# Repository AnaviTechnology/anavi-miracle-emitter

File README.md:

# ANAVI Miracle Emitter

Open source hardware IoT for controlling addressable RGB LED strips (like WS2812B) with XIAO ESP32C3, I2C sensors and mini OLED display.

# License

The project is released under the [Creative Commons Attribution-ShareAlike 4.0 International (CC BY-SA 4.0)](https://creativecommons.org/licenses/by-sa/4.0/).

Note: This is a human-readable summary of (and not a substitute for) the [license](https://creativecommons.org/licenses/by-sa/4.0/legalcode).

You are free to:

Share — copy and redistribute the material in any medium or format Adapt — remix, transform, and build upon the material for any purpose, even commercially. The licensor cannot revoke these freedoms as long as you follow the license terms. Under the following terms:

Attribution — You must give appropriate credit, provide a link to the license, and indicate if changes were made. You may do so in any reasonable manner, but not in any way that suggests the licensor endorses you or your use. ShareAlike — If you remix, transform, or build upon the material, you must distribute your contributions under the same license as the original. No additional restrictions — You may not apply legal terms or technological measures that legally restrict others from doing anything the license permits. Notices:

You do not have to comply with the license for elements of the material in the public domain or where your use is permitted by an applicable exception or limitation. No warranties are given. The license may not give you all of the permissions necessary for your intended use. For example, other rights such as publicity, privacy, or moral rights may limit how you use the material.

You will have to provide a link to the original creator of the project http://www.anavi.technology on any documentation or website.

Credit can be attributed through a link to the creator website: http://www.anavi.technology

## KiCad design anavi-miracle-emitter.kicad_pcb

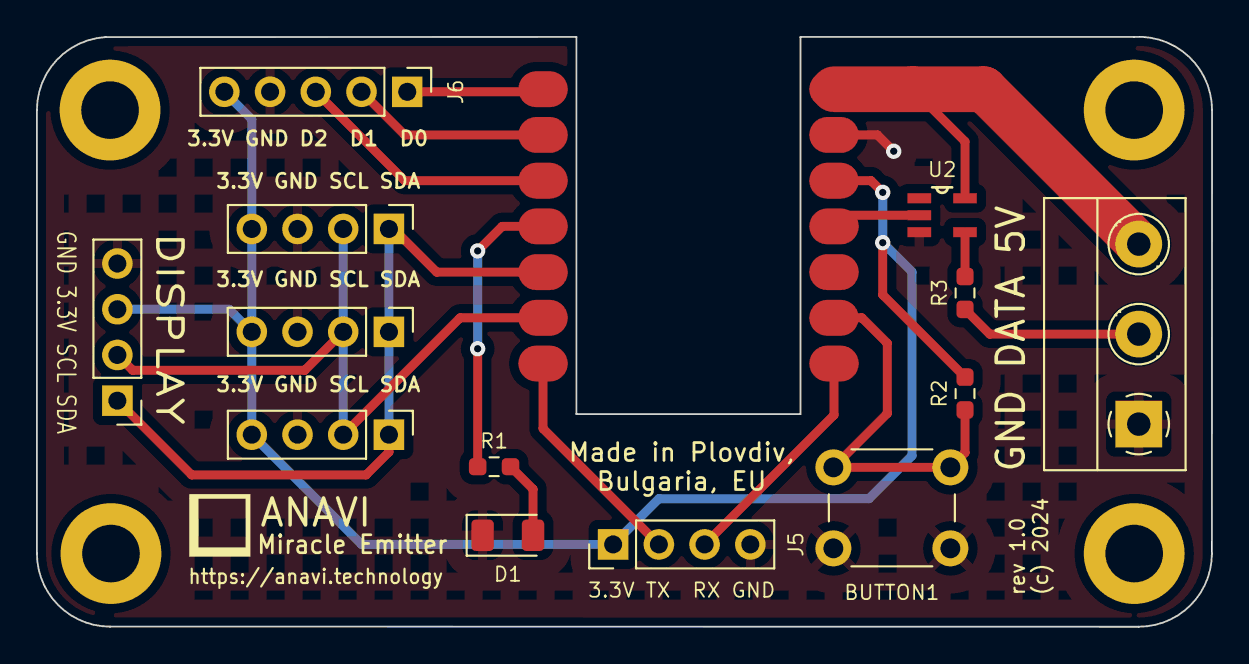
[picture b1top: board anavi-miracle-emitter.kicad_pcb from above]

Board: 2 copper layers, 65.3 x 32.8 mm, 14 parts (0 on the bottom side), 16 nets.

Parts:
BUTTON1: SW_DIP_x01; SW_PUSH_6mm_H4.3mm
D1: KP-3216EC; LED_1206_3216Metric
J1, J2, J3, J4: Conn_01x04_Female; PinHeader_1x04_P2.54mm_Vertical
J5: Conn_01x04_Male; PinHeader_1x04_P2.54mm_Vertical
J6: Conn_01x05_Male; PinHeader_1x05_P2.54mm_Vertical
J7: Screw_Terminal_01x03; TerminalBlock_Phoenix_MKDS-1,5-3_1x03_P5.00mm_Horizontal
R1: 68R; R_0603_1608Metric_Pad0.98x0.95mm_HandSolder
R2: 2K; R_0603_1608Metric_Pad0.98x0.95mm_HandSolder
R3: 330R; R_0603_1608Metric_Pad0.98x0.95mm_HandSolder
U1: MOUDLE-SEEEDUINO-XIAO-ESP32C3; MOUDLE14P-SMD-2.54-21X17.8MM
U2: 74LVC1G17W5-7; SOT95P280X145-5N

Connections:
+3V3: J1.4, J2.4, J3.4, J4.3, J5.1, J6.5, R2.2, U1.12 (3V3)
+5V: J7.3, U1.14 (5V), U2.5 (VCC)
GND: BUTTON1.1, D1.1 (K), J1.3, J2.3, J3.3, J4.4, J5.4, J6.4, J7.1, U1.13 (GND), U2.3 (GND)
unnamed: D1.2 (A), R1.2
unnamed: J1.1, J2.1, J3.1, J4.1, U1.5 (PA8_A4_D4_SDA)
unnamed: J1.2, J2.2, J3.2, J4.2, U1.6 (PA9_A5_D5_SCL)
unnamed: J5.2, U1.7 (PB08_A6_D6_TX)
unnamed: J5.3, U1.8 (PB09_A7_D7_RX)
unnamed: J6.1, U1.1 (PA02_A0_D0)
unnamed: J6.2, U1.2 (PA4_A1_D1)
unnamed: J6.3, U1.3 (PA10_A2_D2)
unnamed: J7.2, R3.2
unnamed: R1.1, U1.4 (PA11_A3_D3)
unnamed: BUTTON1.2, R2.1, U1.9 (PA7_A8_D8_SCK)
unnamed: R3.1, U2.4 (Y)
unnamed: U1.11 (PA6_A10_D10_MOSI), U2.2 (A)

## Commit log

2024-01-21 ANAVI Miracle Emitter
    Initial commit. Work in progress.
2024-01-21 Update PCB
    Update PCB routing and edge cuts.
2024-02-11 Add enclosure
    Add top and bottom parts for enclosure of ANAVI Miracle Emitter.
2024-05-27 anavi-miracle-emitter-assembly-guide.pdf: Add
    Add PDF for assembly guide of components.

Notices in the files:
anavi-miracle-emitter.kicad_pcb:
(c) 2024
